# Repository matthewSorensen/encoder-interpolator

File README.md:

# Encoder Interpolator Board

*A Sorensen Heavy Industries production.*

## What Is It?

This project contains source files for hardware designed to interface with industry-standard 1vpp analog-output sin/cos encoders, and convert their output into a high-resolution interpolated digital quadrature signal. It uses iC-Haus' [iC-TW8](https://www.ichaus.de/product/ic-tw8/) 16-bit sin/cos interpolator IC in order to do this, and has an interface compatible with Renishaw's [REE analog interpolators](https://www.renishaw.com/resourcecentre/download/data-sheet-ree-analogue-interface--18359). However, unlike the REE series, it isn't limited to a fixed factory-set resolution and has a SPI interface.

## Revision History

### Revision 2

Cyrus Lloyd kindly pointed out that the rev 0/1 output connector pinout actually bears absolutely no resemblance to the REE family interface - a minor oversight with no functional consequences, clearly, and not a failure of the entire raison d'être of the project. Revision 2 fixes this, but is as of yet untested.

### Revision 1

Although revision 0 is fully functional, hardware is never perfect (see revision 2). Revision 1 contains two minor changes:

  * The package and footprint of the MEMS oscillator used to generate an on-board 24MHz clock signal was changed from a large 7x5mm package
    (with an incorrect footprint prone to solder bridging) to a smaller 5x3.2mm package with a correct footprint.

  * The 5v power rail indicator LED was removed, as the 3.3v rail also has an indicator that implies a functional 5v rail. All of the remaining
    indicator LEDs' current-limiting resistors are now integrated into one 20K Ohm resistor network, simplifying assembly.

## Fabrication

This cost ($18) and limited availability of the main IC on this board essentially rules out simply ordering finished boards from the usual low-cost PCBA vendors, so  hand assembly is the best option for populating this board. I ordered r0 boards from PCBWAY in their usual-spec 4 layer process (HASL, 1oz Cu), along with a stainless steel solder stencil, placed all of the front-side components by hand, and reflowed the board on a 30x30mm Miniware hotplate. Despite getting very clean solder paste prints and otherwise perfect reflow, I consistently got solder bridges on the QFN-48 package - although easily fixed with an iron, some combination of Kicad's footprints, my stencil thickness, and my solder paste resulted in a bit too much solder.

### Bom

|Reference                                  |Qty|Value                 |Footprint    |Manufacturer      |MPN                 |Mouser PN               |Notes                                    |
|:----------------------------------------- |:-:|:-------------------- |:-----------:|:----------------:|:------------------:|:----------------------:|-----------------------------------------|
|                C1, C2, C3                 | 3 |   47pF 10V C0G 5%    |0603 imperial|      Wurth       |    885012006006    |    710-885012006006    |                                         |
|          C4, C5, C6, C7, C8, C9           | 6 |   470pF 10V C0G 5%   |0603 imperial|      Wurth       |    885012006012    |    710-885012006012    |                                         |
|                 C10, C17                  | 2 |   10uF 25V X5R 10%   |0805 imperial|     Samsung      |  CL21A106KAYNFNE   |  187-CL21A106KAYNFNE   |                                         |
|C11, C12, C13, C14, C15, C16, C18, C20, C22| 9 |   0.1uF 25V X7R 5%   |0603 imperial|   Taiyo Yuden    |  EMK107B7104KA-T   |  963-EMK107B7104KA-T   |                                         |
|                    C19                    | 1 |   22uF 25V X5R 10%   |1206 imperial|     Samsung      |  CL31A226KAHNNNF   |  187-CL31A226KAHNNNF   |                                         |
|                    C21                    | 1 |   1uF 16V X7R 10%    |0603 imperial|       TDK        |CGA3E1X7R1C105K080AC|810-CGA3E1X7R1C105K080AC|                                         |
|                    D1                     | 1 |     Red 0603 LED     |0603 imperial|      Wurth       |   150060RS75000    |   710-150060RS75000    |                                         |
|                  D2, D3                   | 2 |    Blue 0603 LED     |0603 imperial|      Wurth       |   150060BS75000    |   710-150060BS75000    |                                         |
|                    D5                     | 1 |    Green 0603 LED    |0603 imperial|      Wurth       |   150060GS75000    |   710-150060GS75000    |                                         |
|                    FB1                    | 1 |Ferrite Bead 60Ohm 25%|0805 imperial|Murata Electronics|   BLM21PG600SN1D   |     81-BLM21P600S      |                                         |
|                    J1                     | 1 | DA15 Male Horizontal |             |      Wurth       |    618015231421    |    710-618015231421    |                                         |
|                    J2                     | 1 |DA15 Female Horizontal|             |      Wurth       |    618015231121    |    710-618015231121    |                                         |
|                R1, R2, R3                 | 3 |         120R         |0603 imperial|    Panasonic     |    ERJ-S03J121V    |    667-ERJ-S03J121V    |                                         |
|        R4, R5, R6, R7, R8, R9, R19        | 7 |         R1K          |0603 imperial|      Yageo       |   RC0603JR-071KL   |   603-RC0603JR-071KL   |                                         |
|  R10, R11, R12, R13, R14, R15, R16, R17   | 6 |       various        |0805 imperial|                  |                    |                        |See "Configuration" section for values   |
|                    R20                    | 1 |         R20K         |0603 imperial|      Yageo       |  RC0603JR-0720KL   |  603-RC0603JR-0720KL   |                                         |
|               RN1, RN2, RN3               | 3 |         R10K         |  quad 0603  |      Yageo       |  YC164-JR-1010KL   |  603-YC164-JR-1010KL   |                                         |
|                    RN4                    | 1 |         R20K         |  quad 0603  |      Yageo       |  YC164-JR-0720KL   |  603-YC164-JR-0720KL   |                                         |
|                    SW1                    | 1 |SMT push button switch|             |       C&K        |  KMR232NG ULC LFS  |   611-KMR232NGULCLFS   |                                         |
|                  U1, U2                   | 2 |       UA9638C        |SOIC-8 1.27mm|Texas Instruments |     UA9638CDR      |     595-UA9638CDR      |                                         |
|                    U3                     | 1 |        ICTW8         |QFN-48 0.5mm |     iC-Haus      |       ICTW8        |                        |Puchased in Q5 through the US distributor|
|                    U5                     | 1 |      24AA02-OT       |  SOT-23-5   |    Microchip     |     24AA02-OT      |   579-24AA02E48TIOT    |                                         |
|                    U6                     | 1 |   MCP1754S-3302xMB   |  SOT-89-3   |    Microchip     |  MCP1754ST3302EMB  |  579-MCP1754ST3302EMB  |                                         |
|                    X1                     | 1 | DSC1001BE5-024.0000  |   5x3.2mm   |    Microchip     |DSC1001BE5-024.0000 |   579-001BE50240000    |                                         |

## Configuration

The encoder interpolator boards may be configured in two ways: in hardware, via three jumpers and 8 configuration resistors, and in software, over a SPI
bus. The SPI command reference for this chip is only available via request from iC-Haus (in the "iC-TW8 16-BIT SIN/COS INTERPOLATOR Programmer’s Reference" document)
and will not be discussed further. Note that iC-Haus prefers totally-legitimate-seeming corporate email accounts. The full documentation for hardware-configurable
settings is available in the public datasheet, and a subset is reproduced here.

After changing any settings or a new encoder, running the auto-calibration routine is recommended, and may be accomplished by holding down the push button, moving the encoder through a number of cycles, and releasing the button.

### Jumper Settings

Three solder jumpers are located on the back of the PCB.

  * **JP1** controls the drive voltage for the RS-422 ICs. In the default state it is closed and uses the system's 5V rail. If a different drive voltage
  is desired, this jumper may be cut and power supplied to the V422 pin header. If multiple boards are chained together and a different voltage is used,
  this jumper must be open on all of the boards.

  * **JP2** controls the use of an external clock signal to synchronize multiple boards, provided on the CLK pin header. In the default state, the system's internal clock is used. If
  the jumper is cut and soldered in the other position, the internal clock is ignored and the external clock signal is used. If the jumper is not cut, but
  all three pins are connected, the internal clock will be distributed over the CLK pin - it's unclear if this is a good idea, as the local clock oscillators
  don't have particularly high drive strengths. If the jumper is cut and not soldered in the other position, nothing will work. Don't do that.

  * **JP3** controls the configuration mode of the iC-TW8. In its default state, the IC's configuration is taken from the 8 configuration resistors. If
  this jumper is cut, the IC must be configured over SPI.

### Resistor Settings

Resistors R10-R17 are arranged to form four resistor dividers, generating configuration voltages that control the iC-TW8's interpolation factor and signal
processing modes.

|Configuration Value | R_Top | R_Bottom | Function(s)          |
|:--------------------:|:-------:|:----------:|----------------------|
| C0                   | R10     | R11        | Interpolation factor |
| C1                   | R12     | R13        | Interpolation group, Auto-adaption Mode |
| C2                   | R14     | R15        | Hysteresis, Filtering Mode|
| C3                   | R16     | R17        | Output Frequency Limit,  Lag Recovery |

Each resistor divider may output one of twelve voltage levels, set with resistor values recommended by iC-Haus.

| Level | Ratio | R_Top (kΩ) | R_Bottom (kΩ) |
|-------|-------|:------------:|:---------------:|
|11 | 1.00 | 0.00 | ∞   |
|10 | 0.80 | 3.01 | 12.1|
|9  | 0.73 | 4.02 | 11.0|
|8  | 0.67 | 4.99 | 10.0|
|7  | 0.60 | 6.04 | 9.09|
|6  | 0.54 | 6.98 | 8.06|
|5  | 0.46 | 8.06 | 6.98|
|4  | 0.40 | 9.09 | 6.04|
|3  | 0.33 | 10.0 | 4.99|
|2  | 0.27 | 11.0 | 4.02|
|1  | 0.20 | 12.1 | 3.01|
|0  | 0.00 | ∞    | 0.00|

Depending on the interpolation group value of C1, a fixed value for C0 results in different interpolation values:

| C0 Voltage Level | Interpolation Group 0 | Interpolation Group 1 | Interpolation Group 2 |
| :---: | :---: | :---: | :---: |
|11| x8192 | x1600 |**x10000**|
|10| x4096 | x800  |**x5000** |
|9 | x2048 | x400  | x2500    |
|8 | x1024 | x200  | x1250    |
|7 | x512  | x160  | x1000    |
|6 | x256  | x100  | x500     |
|5 | x128  | x80   | x250     |
|4 | x64   | x50   | x125     |
|3 | x32   | x40   | x62.5    |
|2 | x16   | x20   | x25      |
|1 | x8    | x10   |**x12.5** |
|0 | x4    | x5    |**x6.25** |

Values in **bold** have limitations detailed in the full datasheet.

C1 controls both the interpolation group in the previous table and how much clever signal processing the IC is performing - its auto-adaption mode. The following table gives the required voltage level for C1 as a function of desired interpolation group (row) and adaption mode (column).

|Interpolation Group | A3/Full analog/digital | A2 / Full digital (Recommended) | A1/Partial digital | A0 / None |
|:---:| :---:| :---:|:---:|:---:|
| **Group 0** | 9 | 6 | 3 | 0 |
| **Group 1** | 10 | 7 | 4 | 1 |
| **Group 2** | 11 | 8 | 5 | 2 |

C2 controls hysteresis and filtering of the AB outputs - again, the following table gives the required voltage level as a function of the desired hysteresis (row) and filtering (column).

|Hysteresis (AB Edge Count) | Heavy Filtering | Normal Filtering (Recommended) | Minimal Filtering |
|:---:| :---:| :---:|:---:|
|**1**| 11 | 7 | 3 |
|**2**| 10 | 6 | 2 |
|**4**| 9  | 5 | 1 |
|**8**| 8  | 4 | 0 |

C3 controls AB output frequency (row) and lag recovery (column).

| Maximum AB Frequency | Maximum AB Frequency (24MHz clock) | Lag Recovery Enabled | Lag Recovery Disabled (Recommended) |
|:---:| :---:| :---:|:---:|
|*f<sub>clock</sub>*/8 | 3.0 MHz | 11 | 5 |
|*f<sub>clock</sub>*/16 | 1.0 MHz | 10 | 4 |
|*f<sub>clock</sub>*/32 | 0.75 MHz | 9 | 3 |
|*f<sub>clock</sub>*/64 | 0.375 MHz | 8 | 2 |
|*f<sub>clock</sub>*/128 | 187.5 KHz | 7 | 1 |
|*f<sub>clock</sub>*/256 | 93.75 KHz | 6 | 0 |

## Future Directions

As this board was designed for a specific application that revision 0 satisfies, it's unlikely to see significant further changes. However, the choice of 3.3v as a system
voltage leaves quite a bit of performance on the table by limiting the clock speed to 24MHz, instead of 32MHz. This choice was made for comparability with the REE pinouts,
which only have a 5V supply - ideally, the noisy RSS-422 drivers would live on a separate voltage rail than the main IC voltage supply.

A library for SPI communication with the IC is a more likely future outcome.

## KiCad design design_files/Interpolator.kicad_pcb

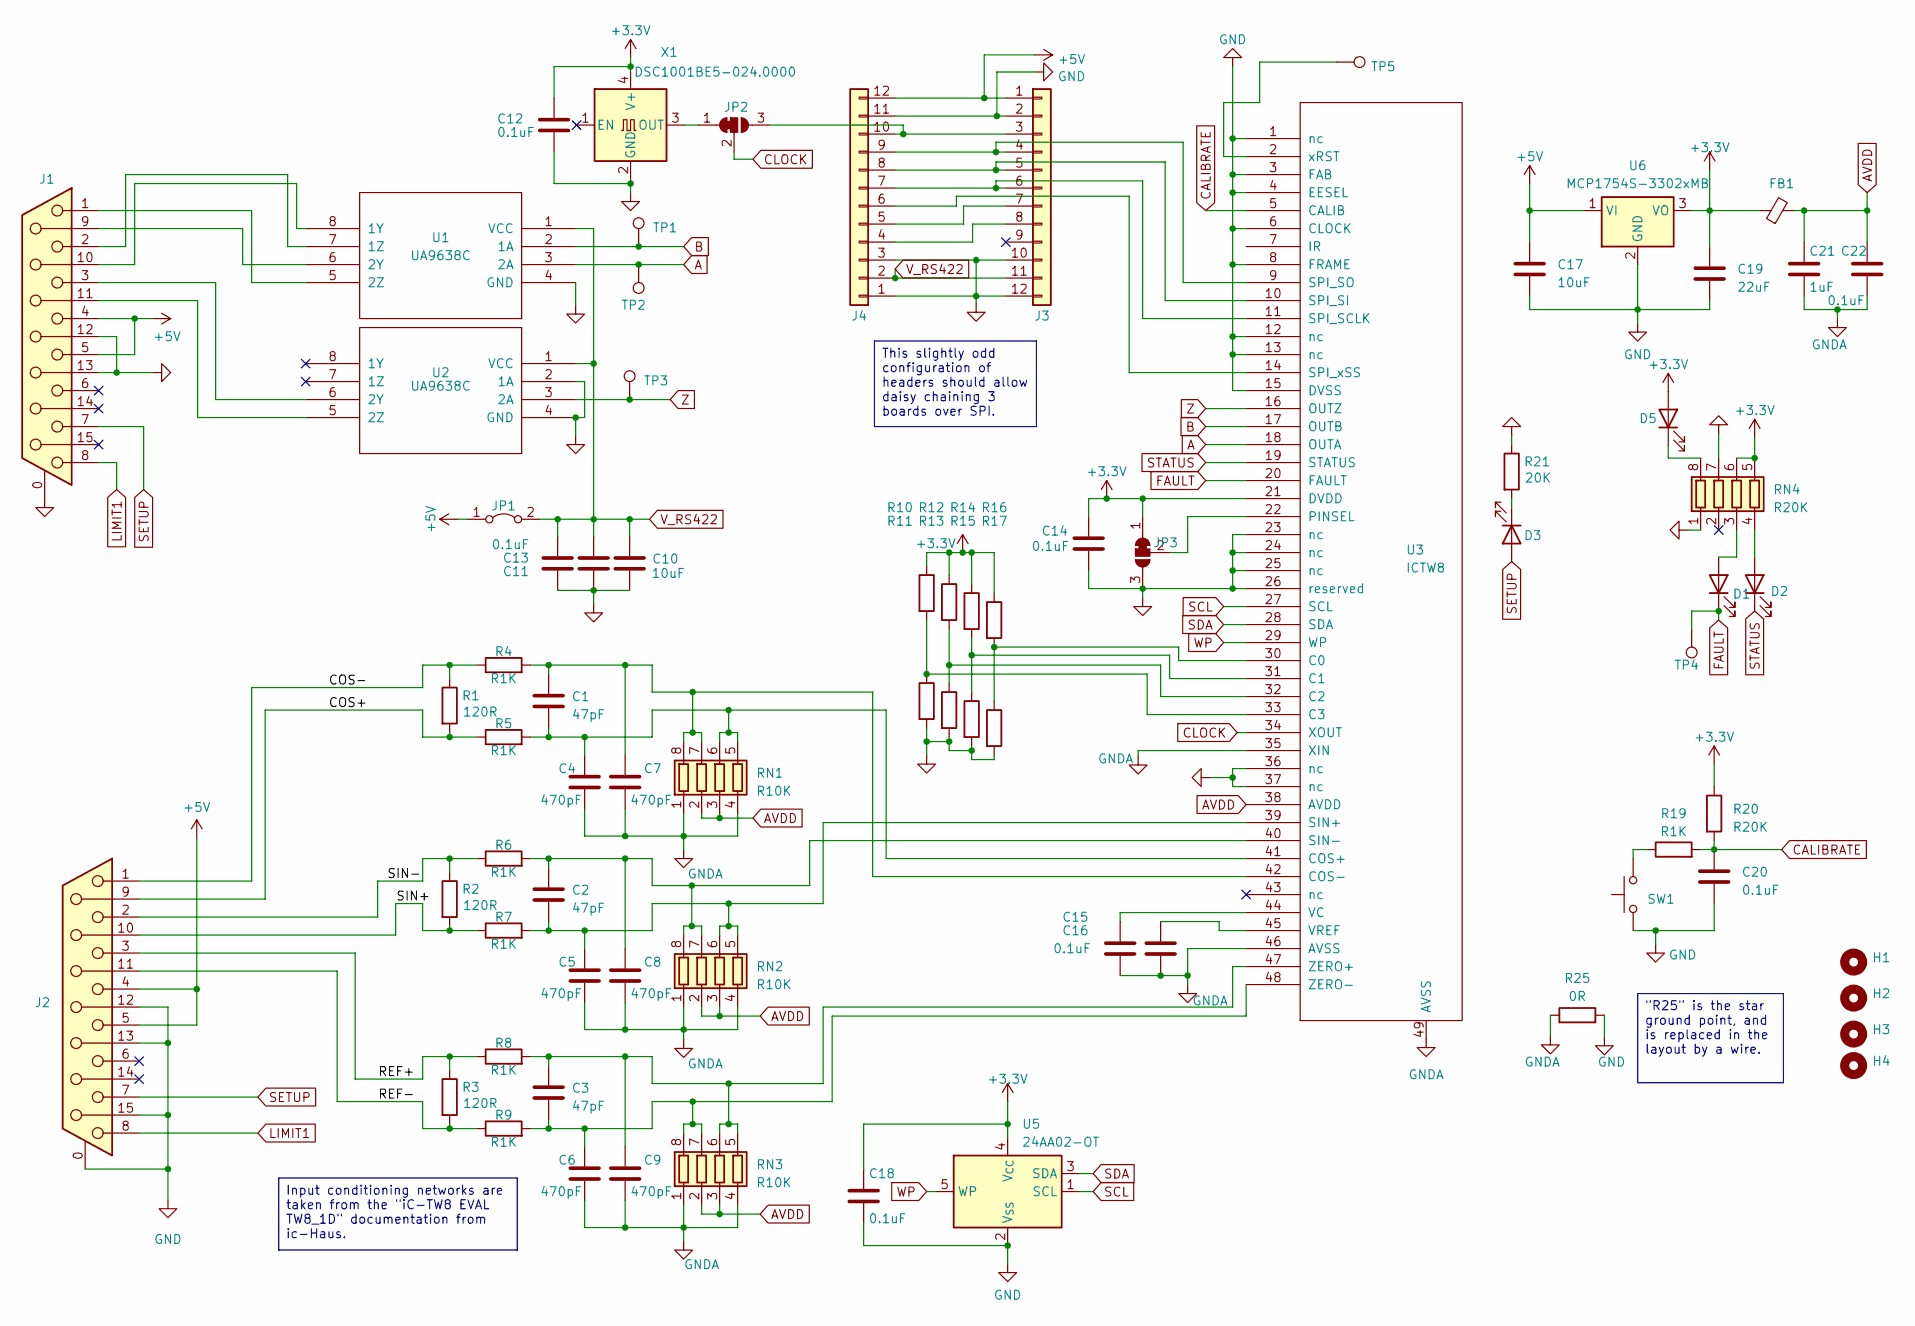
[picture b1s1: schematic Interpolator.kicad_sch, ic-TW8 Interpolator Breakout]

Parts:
C1, C2, C3: 47pF; C_0603_1608Metric
C4, C5, C6, C7, C8, C9: 470pF; C_0603_1608Metric
C10, C17: 10uF; C_0805_2012Metric
C11, C12, C13, C14, C15, C16, C18, C20, C22: 0.1uF; C_0603_1608Metric
C19: 22uF; C_1206_3216Metric
C21: 1uF; C_0603_1608Metric
D1, D2, D3, D5: LED; LED_0603_1608Metric_Pad1.05x0.95mm_HandSolder
FB1: FerriteBead_Small; R_0805_2012Metric
H1, H2, H3, H4: MountingHole; MountingHole_3.2mm_M3
J1: DA15_Receptacle_MountingHoles; DSUB-15_Male_Horizontal_P2.77x2.84mm_EdgePinOffset9.90mm_Ho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
J2: DA15_Receptacle_MountingHoles; DSUB-15_Female_Horizontal_P2.77x2.84mm_EdgePinOffset9.90mm_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
J3, J4: Conn_01x12; PinHeader_1x12_P2.54mm_Horizontal
JP1: Jumper_2_Bridged; SolderJumper-2_P1.3mm_Bridged2Bar_Pad1.0x1.5mm
JP2, JP3: SolderJumper_3_Bridged12; SolderJumper-3_P1.3mm_Bridged12_RoundedPad1.0x1.5mm
R1, R2, R3: 120R; R_0603_1608Metric
R4, R5, R6, R7, R8, R9, R19: R1K; R_0603_1608Metric
R10, R11, R12, R13, R14, R15: R; R_0805_2012Metric
R16: 10K; R_0805_2012Metric
R17: 4.99K; R_0805_2012Metric
R20: R20K; R_0603_1608Metric
R21: 20K; R_0603_1608Metric
R25: 0R; R_0201_0603Metric
RN1, RN2, RN3: R10K; R_Array_Convex_4x0603
RN4: R20K; R_Array_Convex_4x0603
SW1: SW_Push; SW_Push_1P1T_NO_CK_KMR2
TP1, TP2, TP3, TP4, TP5: TestPoint; TestPoint_Pad_D1.0mm
U1, U2: UA9638C; SOIC-8_3.9x4.9mm_P1.27mm
U3: ICTW8; QFN-48-1EP_7x7mm_P0.5mm_EP5.45x5.45mm
U5: 24AA02-OT; SOT-23-5
U6: MCP1754S-3302xMB; SOT-89-3
X1: DSC1001BE5-024.0000; Oscillator5x3.2mm

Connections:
+3.3V: C12.1, C14.1, C18.1, C19.1, D5.2 (A), FB1.1, JP3.1 (A), R10.1, R12.1, R14.1, R16.1, R20.1, RN4.5 (R4.2), RN4.6 (R3.2), U3.21 (DVDD), U5.4 (V_{CC}), U6.3 (VO), X1.4 (V+)
+5V: C17.1, J1.4, J1.5, J2.4, J2.5, J3.1, J4.12, JP1.1 (A), U6.1 (VI)
/COS+: J2.9, R1.2, R5.1
/COS-: J2.1, R1.1, R4.1
/REF+: J2.3, R3.1, R8.1
/REF-: J2.11 (P111), R3.2, R9.1
/SIN+: J2.10, R2.2, R7.1
/SIN-: J2.2, R2.1, R6.1
A: TP2.1, U1.3 (2A), U3.18 (OUTA)
AVDD: C21.1, C22.1, FB1.2, RN1.2 (R2.1), RN1.3 (R3.1), RN2.2 (R2.1), RN2.3 (R3.1), RN3.2 (R2.1), RN3.3 (R3.1), U3.38 (AVDD)
B: TP1.1, U1.2 (1A), U3.17 (OUTB)
CALIBRATE: C20.1, R19.2, R20.2, U3.5 (CALIB)
CLOCK: JP2.2 (C), U3.34 (XOUT)
FAULT: D1.1 (K), TP4.1, U3.20 (FAULT)
GND: C10.1, C11.1, C12.2, C13.1, C14.2, C17.2, C18.2, C19.2, C20.2, J1.0 (PAD), J1.12, J1.13, J2.0 (PAD), J2.12, J2.13, J2.15, J3.2, J3.10, J3.12, J4.1, J4.3, J4.11, JP3.3 (B), R11.2, R13.2, R15.2, R17.2, R21.1, R25.2, RN4.1 (R1.1), RN4.7 (R2.2), SW1.1, U1.4 (GND), U2.2 (1A), U2.4 (GND), U3.1 (nc), U3.3 (FAB), U3.4 (EESEL), U3.6 (CLOCK), U3.8 (FRAME), U3.12 (nc), U3.13 (nc), U3.15 (DVSS), U3.23 (nc), U3.24 (nc), U3.25 (nc), U3.26 (reserved), U3.36 (nc), U3.37 (nc), U5.2 (V_{SS}), U6.2 (GND), X1.2 (GND)
GNDA: C4.2, C5.2, C6.2, C7.2, C8.2, C9.2, C15.2, C16.2, C21.2, C22.2, R25.1, RN1.1 (R1.1), RN1.4 (R4.1), RN2.1 (R1.1), RN2.4 (R4.1), RN3.1 (R1.1), RN3.4 (R4.1), U3.35 (XIN), U3.46 (AVSS), U3.49 (AVSS)
LIMIT1: J1.8, J2.8
unnamed: D1.2 (A), RN4.3 (R3.1)
unnamed: D2.2 (A), RN4.4 (R4.1)
unnamed: D3.1 (K), R21.2
unnamed: D5.1 (K), RN4.8 (R1.2)
unnamed: J1.9, U1.6 (2Y)
unnamed: J1.10, U1.8 (1Y)
unnamed: J1.11 (P111), U2.5 (2Z)
unnamed: J3.3, J4.10, JP2.3 (B)
unnamed: J3.4, J4.9, U3.9 (SPI_SO)
unnamed: J3.5, J4.8, U3.10 (SPI_SI)
unnamed: J3.6, J4.7, U3.11 (SPI_SCLK)
unnamed: J3.7, J4.5
unnamed: J3.8, J4.4
unnamed: J4.6, U3.14 (SPI_xSS)
unnamed: JP2.1 (A), X1.3 (OUT)
unnamed: JP3.2 (C), U3.22 (PINSEL)
unnamed: R19.1, SW1.2
unnamed: C1.1, C7.1, R4.2, RN1.7 (R2.2), RN1.8 (R1.2), U3.42 (COS-)
unnamed: C1.2, C4.1, R5.2, RN1.5 (R4.2), RN1.6 (R3.2), U3.41 (COS+)
unnamed: C2.1, C8.1, R6.2, RN2.7 (R2.2), RN2.8 (R1.2), U3.40 (SIN-)
unnamed: C2.2, C5.1, R7.2, RN2.5 (R4.2), RN2.6 (R3.2), U3.39 (SIN+)
unnamed: C3.2, C6.1, R9.2, RN3.7 (R2.2), RN3.8 (R1.2), U3.48 (ZERO-)
unnamed: C3.1, C9.1, R8.2, RN3.5 (R4.2), RN3.6 (R3.2), U3.47 (ZERO+)
unnamed: J1.2, U1.7 (1Z)
unnamed: J1.1, U1.5 (2Z)
unnamed: J1.3, U2.6 (2Y)
unnamed: R16.2, R17.1, U3.30 (C0)
unnamed: R14.2, R15.1, U3.31 (C1)
unnamed: R12.2, R13.1, U3.32 (C2)
unnamed: R10.2, R11.1, U3.33 (C3)
unnamed: C15.1, U3.44 (VC)
unnamed: C16.1, U3.45 (VREF)
unnamed: TP5.1, U3.2 (xRST)
SCL: U3.27 (SCL), U5.1 (SCL)
SDA: U3.28 (SDA), U5.3 (SDA)
SETUP: D3.2 (A), J1.7, J2.7
STATUS: D2.1 (K), U3.19 (STATUS)
V_RS422: C10.2, C11.2, C13.2, J3.11, J4.2, JP1.2 (B), U1.1 (VCC), U2.1 (VCC)
WP: U3.29 (WP), U5.5 (WP)
Z: TP3.1, U2.3 (2A), U3.16 (OUTZ)

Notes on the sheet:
"R25" is the star ground point, and is replaced in the layout by a wire.
Input conditioning networks are taken from the "iC-TW8 EVAL TW8_1D" documentation from ic-Haus.
This slightly odd configuration of headers should allow daisy chaining 3 boards over SPI.

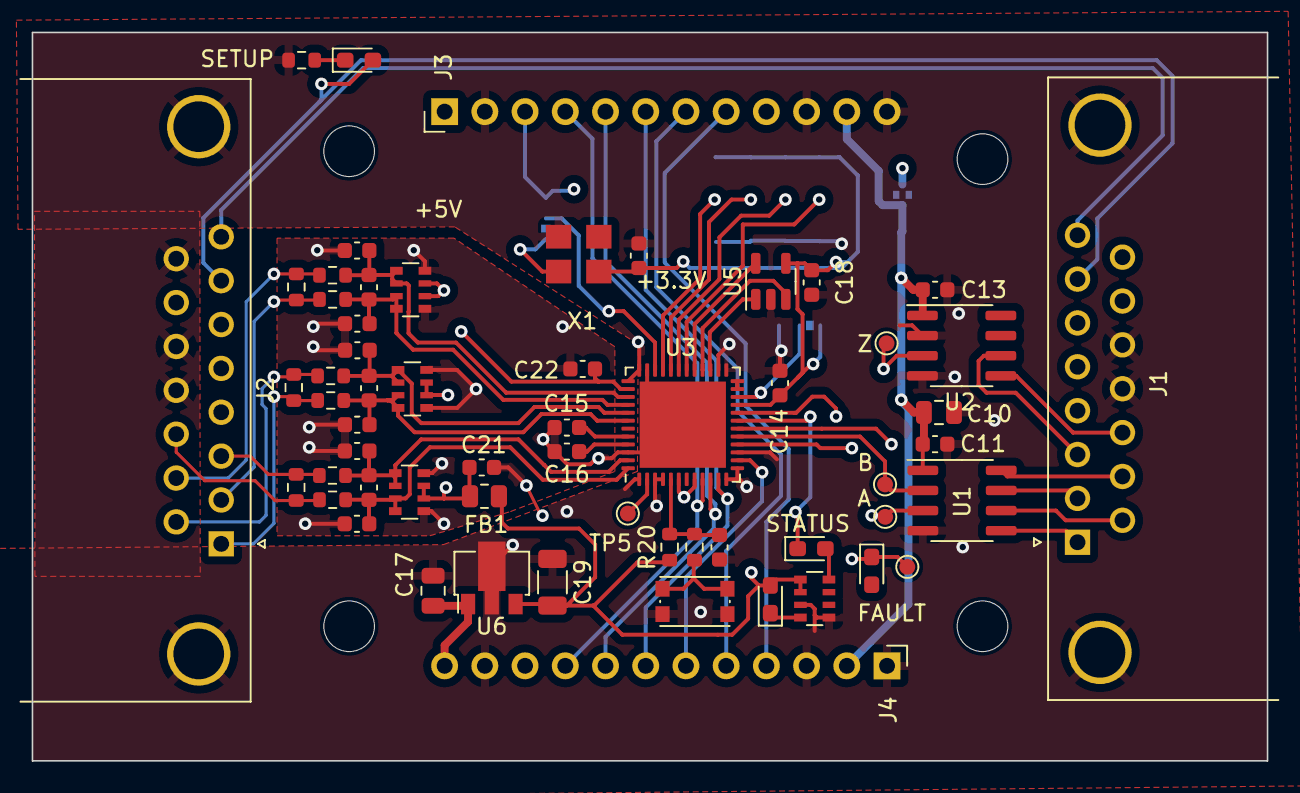
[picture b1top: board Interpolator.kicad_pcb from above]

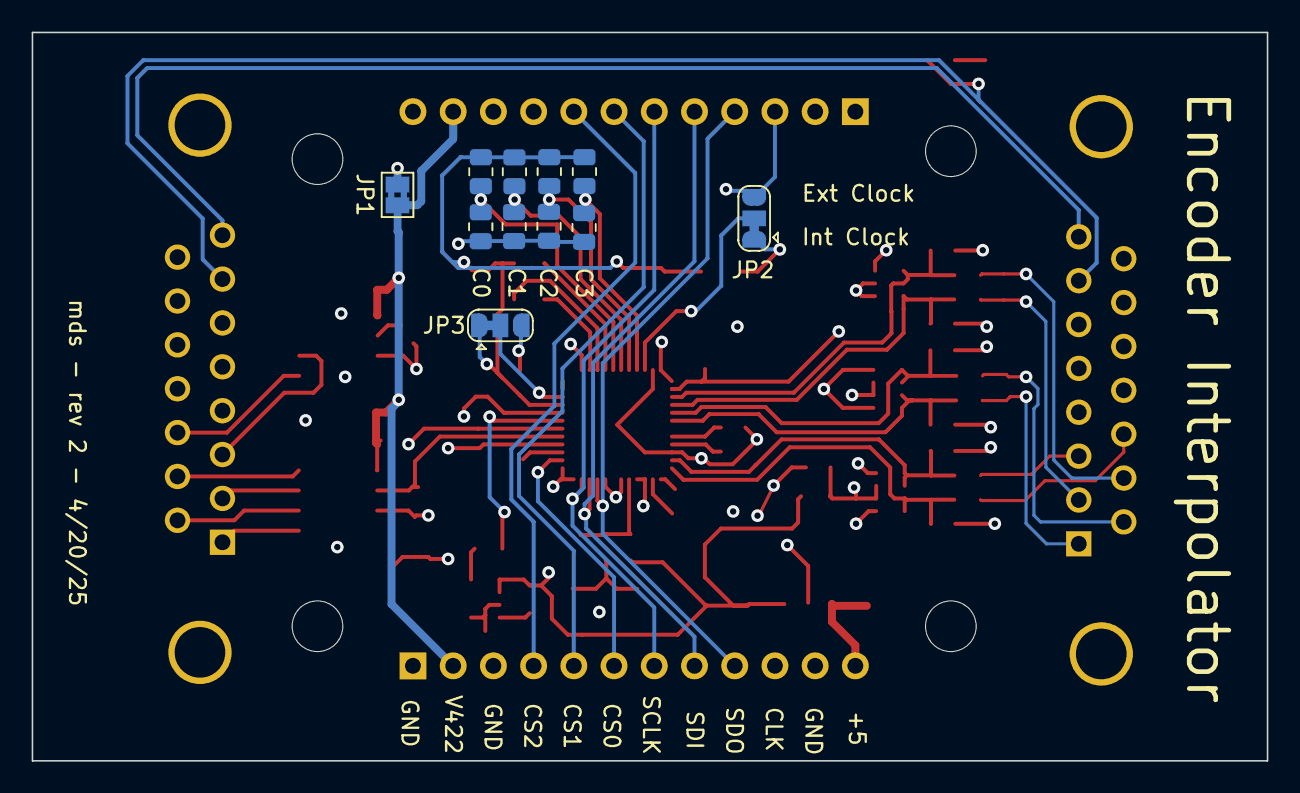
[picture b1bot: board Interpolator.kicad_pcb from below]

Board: 4 copper layers, 78.0 x 46.0 mm, 74 parts (11 on the bottom side), 57 nets.

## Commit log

2025-01-18 Revision 0 of the encoder interpolator project
2025-01-18 Update a few footprints, remove the 5v rail power LED, move all of the LED resistors to one 20K network
2025-01-19 Add a readme and license
2025-01-19 Add another pretty picture
2025-01-19 Change the markdown subscript
2025-01-22 Add a BOM and fab notes
2025-04-20 Revision 2, and update kicad version
2025-04-20 Pulldown the unused line driver input
